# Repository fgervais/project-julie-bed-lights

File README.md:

# RGB LED Strip Controller

## Main Board

## Early Tests with LED Strip

## Installed

## App

This project is entirely controlled through the phone app. 

The QR code can be used to get a copy of this Blink project.

Blynk Project | Blynk Project Clone QR
:-------------------------:|:-------------------------:
  |

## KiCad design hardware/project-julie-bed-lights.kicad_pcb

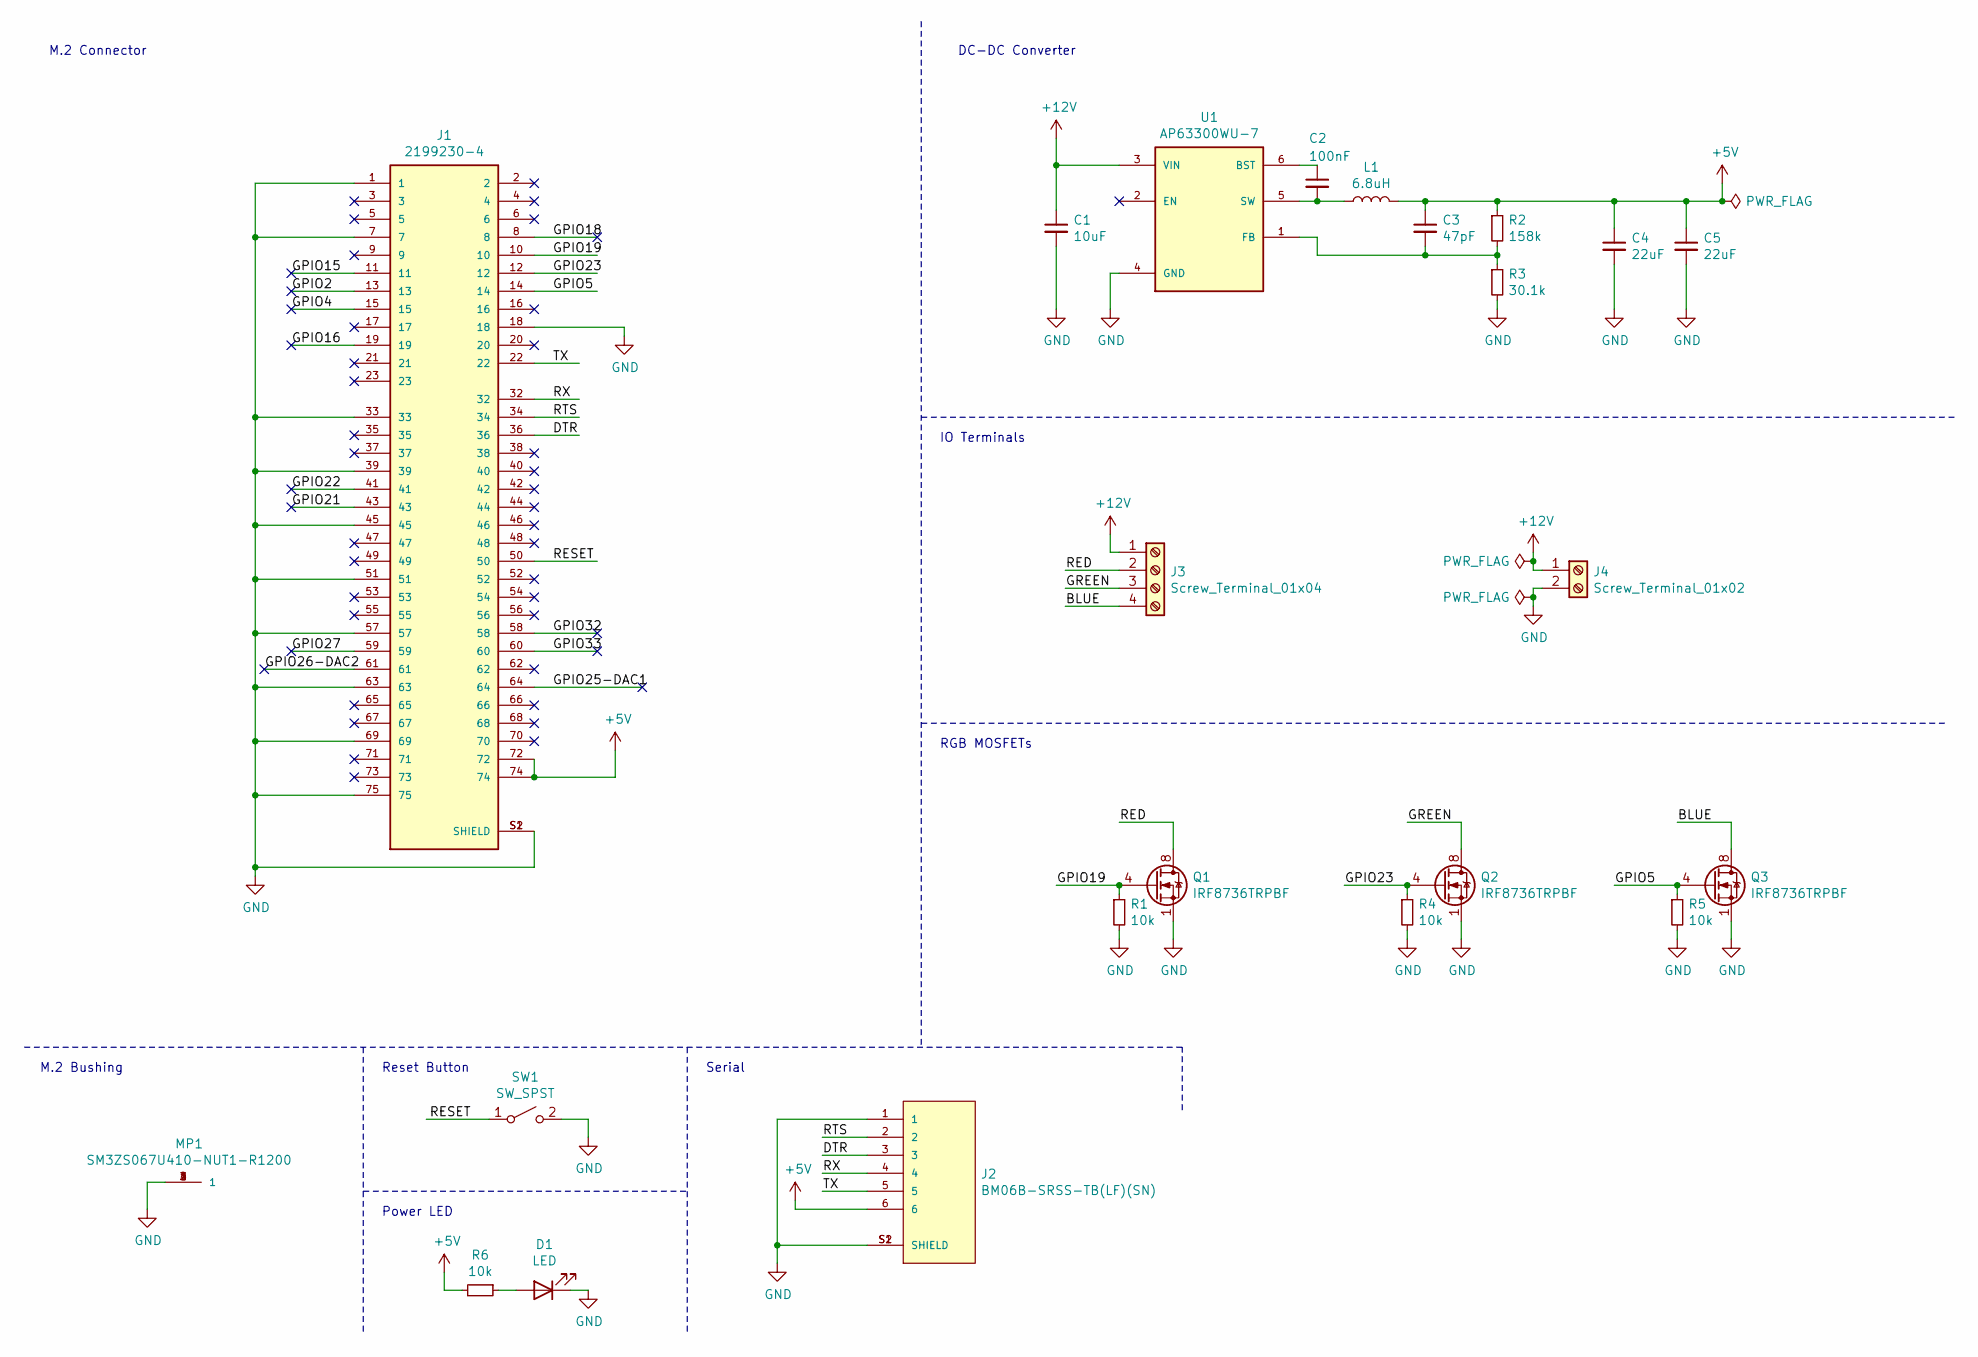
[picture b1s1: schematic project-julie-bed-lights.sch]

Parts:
C1: 10uF; C_1210_3225Metric_Pad1.33x2.70mm_HandSolder
C2: 100nF; C_0603_1608Metric
C3: 47pF; C_0603_1608Metric
C4, C5: 22uF; C_1210_3225Metric_Pad1.33x2.70mm_HandSolder
D1: LED; LED_0603_1608Metric
J1: 2199230-4; TE_2199230-4
J2: BM06B-SRSS-TB(LF)(SN); JST_BM06B-SRSS-TB(LF)(SN); PARTREV NA
J3: Screw_Terminal_01x04; Molex-393570004-MFG
J4: Screw_Terminal_01x02; Molex-393570002-MFG
L1: 6.8uH; IND_SRP4020TA-6R8M
MP1: SM3ZS067U410-NUT1-R1200; JAE_SM3ZS067U410-NUT1-R1200; PARTREV 2
Q1, Q2, Q3: IRF8736TRPBF‎; SOIC-8_3.9x4.9mm_P1.27mm
R1, R4, R5, R6: 10k; R_0603_1608Metric
R2: 158k; R_0603_1608Metric
R3: 30.1k; R_0603_1608Metric
SW1: SW_SPST; SW_SPST_B3U-1000P
U1: AP63300WU-7; SOT95P280X100-6N; PARTREV 2020-04-24

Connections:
+5V: C3.1, C4.1, C5.1, J1.72, J1.74, J2.6, L1.2, R2.1, R6.2
+12V: C1.1, J3.1, J4.1, U1.3 (VIN)
/BLUE: J3.4, Q3.5 (D), Q3.6 (D), Q3.7 (D), Q3.8 (D)
/DTR: J1.36, J2.3
/GPIO2: J1.13
/GPIO4: J1.15
/GPIO5: J1.14, Q3.4 (G), R5.1
/GPIO15: J1.11
/GPIO16: J1.19
/GPIO18: J1.8
/GPIO19: J1.10, Q1.4 (G), R1.1
/GPIO21: J1.43
/GPIO22: J1.41
/GPIO23: J1.12, Q2.4 (G), R4.1
/GPIO25-DAC1: J1.64
/GPIO26-DAC2: J1.61
/GPIO27: J1.59
/GPIO32: J1.58
/GPIO33: J1.60
/GREEN: J3.3, Q2.5 (D), Q2.6 (D), Q2.7 (D), Q2.8 (D)
/RED: J3.2, Q1.5 (D), Q1.6 (D), Q1.7 (D), Q1.8 (D)
/RESET: J1.50, SW1.1 (A)
/RTS: J1.34, J2.2
/RX: J1.32, J2.4
/TX: J1.22, J2.5
GND: C1.2, C4.2, C5.2, D1.1 (K), J1.1, J1.7, J1.18, J1.33, J1.39, J1.45, J1.51, J1.57, J1.63, J1.69, J1.75, J1.S1 (SHIELD), J1.S2 (SHIELD), J2.1, J2.S1 (SHIELD), J2.S2 (SHIELD), J4.2, MP1.1, MP1.2, MP1.3, MP1.4, Q1.1 (S), Q1.2 (S), Q1.3 (S), Q2.1 (S), Q2.2 (S), Q2.3 (S), Q3.1 (S), Q3.2 (S), Q3.3 (S), R1.2, R3.2, R4.2, R5.2, SW1.2 (B), U1.4 (GND)
unnamed: C2.1, U1.6 (BST)
unnamed: C2.2, L1.1, U1.5 (SW)
unnamed: C3.2, R2.2, R3.1, U1.1 (FB)
unnamed: D1.2 (A), R6.1

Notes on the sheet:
M.2 Bushing
Reset Button
Serial
DC-DC Converter
Power LED
M.2 Connector
IO Terminals
RGB MOSFETs

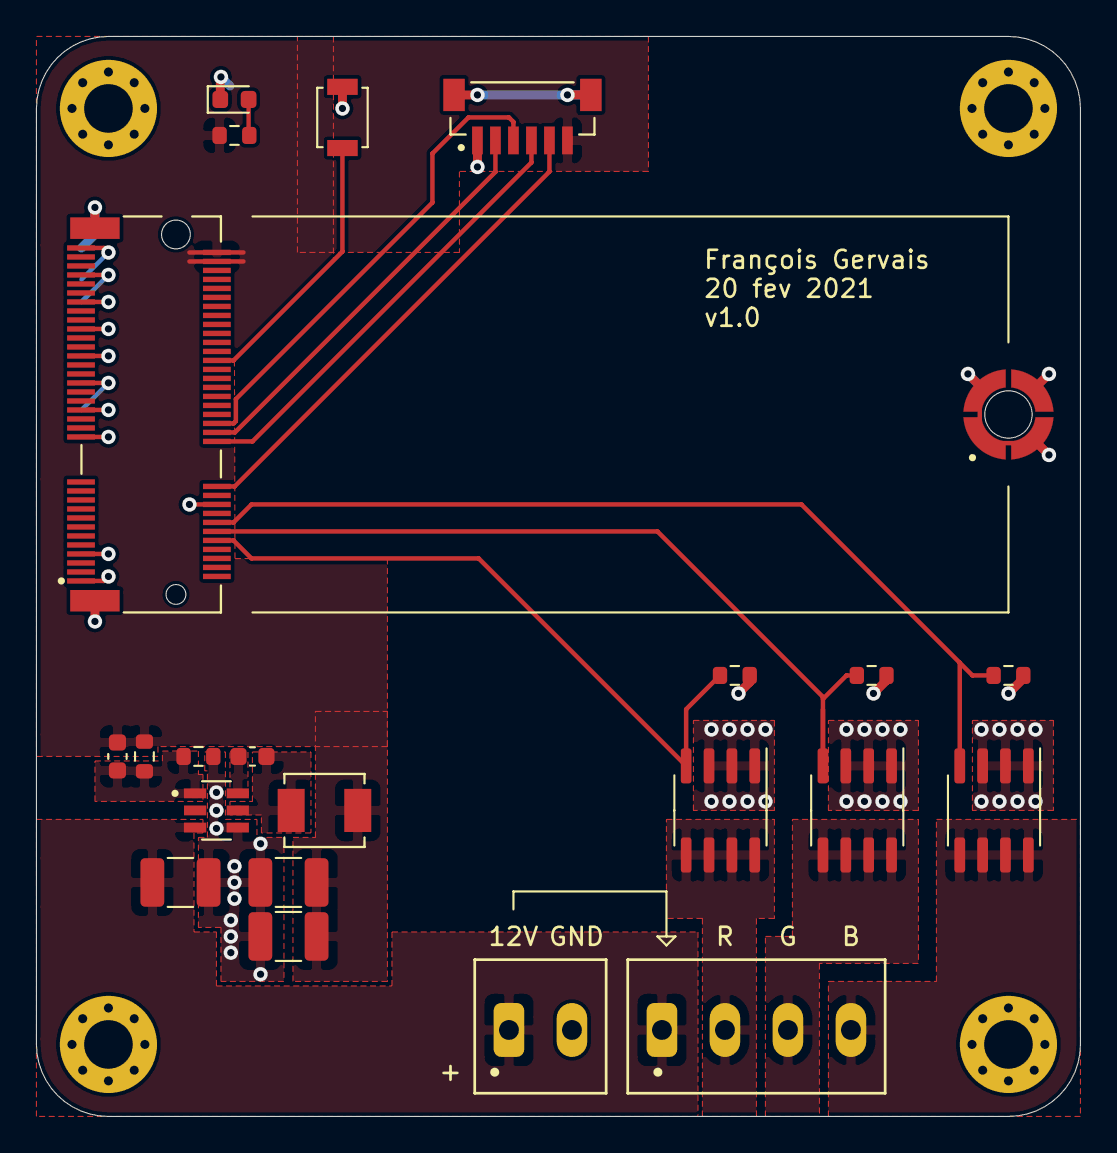
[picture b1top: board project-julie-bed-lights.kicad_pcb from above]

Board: 2 copper layers, 58.0 x 60.0 mm, 23 parts (0 on the bottom side), 18 nets.

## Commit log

2021-02-07 Schematic done except DC-DC converter
2021-02-07 Added DC-DC converter
2021-02-15 Add lib-python submodule
2021-02-15 Set lib-python to SSL
2021-02-15 Test 3 PWMs
2021-02-16 Prepare the app interface
2021-02-17 Connected to Blynk servers
2021-02-19 First placement
2021-02-20 DC-DC converter routing
2021-02-20 First routing except ground
2021-02-21 First routing
2021-02-21 Add version of previous commit
2021-02-25 Fix Conn_Molex_39357000x footprint
2021-03-31 Setup assembly print
2021-04-01 Add polarity marking on power input
2021-04-04 Add overview image
2021-04-08 Enable webrepl
2021-04-08 Add init script
2021-04-08 Fix app sync on boot
2021-04-08 Change pwm freq to 500Hz
2021-04-08 Add screw terminal marking
2021-04-09 Add image with led strip
2021-05-17 Make init port configurable
2021-05-17 Add installed image
2021-05-19 Add app section in README
2021-05-19 Make the app assets smaller
2021-09-20 Add basic esphome project
2021-09-23 esphome: add bulk of the logic
2021-09-24 Update esphome version
2021-09-24 Remove pin comment
2021-09-24 Use IP address for broker
    It seems that there is a bug with resolving the mdns name and I don't
    feel like fixing it for now.
    https://github.com/esphome/issues/issues/2463
2021-10-22 Set MQTT reboot timeout to 3 minutes
